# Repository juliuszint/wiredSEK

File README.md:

# A wired version of the Surface Ergonomic Keyboard from Microsoft.

## Disassembly
**Disclaimer**: These disassembly instructions can not be reversed and result in a broke keyboard. They are only provided as a documentation for other people to read, so that they dont have to brick their keyboard. So with that out of the way lets get started.

The keyboard is held together by an awful lot of glue and some screws. I do not own a heat gun and so i started with carefully using a screwdriver to remove the wrist rest. Even with a heat gun i doubt that it is impossible, to remove it without damaging some plastic. As can be seen in the following image, there is not only glue on the edges, but also in the center of the wrist rest.

The next step is to remove all 10 screws. 4 of them are small and 6 are rather large and threaded into the plastic. Then disconnect the power and paring button connector from the logic board. Next up is getting the screw driver back out and start to remove the keyboard panel from the case. It is held in place by a glue stripe all around the edges, some glue right in the center of the keyboard, and 9 glue spots as one can see in the following image.

4 more large screws hold the logic board cover in place. With them removed we can lift up the logic board and see the 34 pin Flexible Flat Cable (FFC) that connects the keyboard matrix with the logic board. 2 of those 34 lanes are not routed, so only 32 are actually connected.

I hoped that by fully disassembling the keyboard, I would be able to learn more about the keyboard matrix, but this did not turn out to be true. Anyway, after i removed every single plastic rivet and removed the remaining screws, this is how a fully disassembled surface ergonomic keyboard looks like:

Once the metal backplate is removed, the keys can just be popped out. They are still kept in place by small metal sheets and the wires connecting them. With the keyboard fully disassembled, we can now start to measure the keyboard matrix.

## Figuring out the keyboard matrix

With [@Geends](https://github.com/Geend/) logic analyzer and other hardware, we started by probing the logic level of every pin when no key is pressed. Next we toggled every LED (total of 4) one after another and observed the changes. Armed with that information we were able to make a educated guess of the keyboard matrix and with the 16 channel logic analyzer we were able to determine the full keyboard matrix.

Initial testing results:

| Pin Number (top left = 0)| Logic Level without Keypress |                            Function                           |
|:------------------------:|:----------------------------:| --------------------------------------------------------------|
| 0                        |3V                            | Keyboard Matrix: Row 0                                        |
| 1                        |3V                            | Keyboard Matrix: Row 1                                        |
| 2                        |3V                            | Keyboard Matrix: Row 2                                        |
| 3                        |3V                            | Keyboard Matrix: Row 3                                        |
| 4                        |3V                            | Keyboard Matrix: Row 4                                        |
| 5                        |3V                            | Keyboard Matrix: Row 5                                        |
| 6                        |3V                            | Keyboard Matrix: Row 6                                        |
| 7                        |3V                            | Keyboard Matrix: Row 7                                        |
| 8                        |3V                            | NumLink LED - with 3V the LED is off and on with 0.4V         |
| 9                        |3V                            | CapsLock LED - with 3V the LED is off and on with 0.4V        |
| 10                       |GND                           | Not connected                                                 |
| 11                       |1V                            | Pairing LED - White                                           |
| 12                       |1V                            | Pairing LED - Red                                             |
| 13                       |3V                            | LED Vcc                                                       |
| 14                       |0V                            | Keyboard Matrix: Column 0                                     |
| 15                       |0V                            | Keyboard Matrix: Column 1                                     |
| 16                       |0V                            | Keyboard Matrix: Column 2                                     |
| 17                       |0V                            | Keyboard Matrix: Column 3                                     |
| 18                       |0V                            | Keyboard Matrix: Column 4                                     |
| 19                       |0V                            | Keyboard Matrix: Column 5                                     |
| 20                       |0V                            | Keyboard Matrix: Column 6                                     |
| 21                       |0V                            | Keyboard Matrix: Column 7                                     |
| 22                       |0V                            | Keyboard Matrix: Column 8                                     |
| 23                       |0V                            | Keyboard Matrix: Column 9                                     |
| 24                       |0V                            | Keyboard Matrix: Column 10                                    |
| 25                       |0V                            | Keyboard Matrix: Column 11                                    |
| 26                       |0V                            | Keyboard Matrix: Column 12                                    |
| 27                       |0V                            | Keyboard Matrix: Column 13                                    |
| 28                       |0V                            | Keyboard Matrix: Column 14                                    |
| 29                       |0V                            | Keyboard Matrix: Column 15                                    |
| 30                       |0V                            | Keyboard Matrix: Column 16                                    |
| 31                       |3V                            | Fn LED - with 3V the LED is off and on with 0.4V              |
| 32                       |3V                            | Rollen - with 3V the LED is off and on with 0.4V              |
| 33                       |GND                           | Not connected                                                 |

The keyboard matrix from Surface Ergonomic Keyboard with german keys:

|           |    Row-0   |    Row-1   |    Row-2   |    Row-3   |    Row-4   |    Row-5   |    Row-6   |    Row-7   |
|:---------:|:----------:|:----------:|:----------:|:----------:|:----------:|:----------:|:----------:|:----------:|
| Column-0  |Num Entf    |Num 3       |Num 6       |Num 9       |Num \*      |6           |V           |L           |
| Column-1  |Num 0       |Num 2       |Num 5       |Num 8       |Num /       |5           |C           |K           |
| Column-2  |<           |Num 1       |Num 4       |Num 7       |Calc        |Num Enter   |X           |J           |
| Column-3  |Y           |T           |R           |E           |W           |Q           |Pfeil oben  |H           |
| Column-4  |-           |Bild Unten  |Bild Hoch   |Ende        |Num Lock    |Druck       |F12         |Leer        |
| Column-5  |.           |F4          |Entf        |Pos1        |Tab         |Einfg       |F11         |G           |
| Column-6  |,           |#           |0           |            |O           |Num +       |F10         |F           |
| Column-7  |M           |Ä           |9           |+           |i           |\`          |F9          |D           |
| Column-8  |N           |Num -       |8           |Ü           |U           |ß           |F8          |S           |
| Column-9  |Backspace   |Arrow right |7           |P           |Z           |^           |F7          |A           |
| Column-10 |Left Ctrl   |            |            |            |Right Ctrl  |            |            |            |
| Column-11 |            |Left Shift  |            |            |            |Right Shift |            |Fn          |
| Column-12 |            |            |Left ALT    |            |            |            |Alt Gr      |Context Menu|
| Column-13 |Pause       |Rollen      |Chat        |Left WIN    |Lock        |Rechteck    |            |Right WIN   |
| Column-14 |Num Clear   |4           |F1          |F5          |            |3           |Caps Lock   |Arrow Down  |
| Column-15 |            |F2          |F6          |Enter       |F3          |2           |            |Arrow Left  |
| Column-16 |Esc         |            |            |            |            |1           |B           |Ö           |

## Designing the PCB

The most difficult part was to find a MCU due to the chip shortage. From all the compatible controllers that are listed on QMKs website only the AT90USB646 was available. This turned out to be a perfect fit. It is a very simple MCU with enough GPIO pins, USB and a 64-TQFP package can be soldered by hand.

There is not much to say about the schematic itself because there is not a lot more on it then the MCU and a USB jack. There are a lot of testpoints, a power LED that can be disabled with a solder jumper, a status LED and a JTAG interface.

The complete board was designed with the open source software Kicad and tutorials from the Youtube channel Phil's Lab. This [[2]] three hour video is a great resource if someone wants to learn how to create a board from scratch and have it manufactured.

The outline and four holes (two placeholder and two for screws) are required for the circuit board to fit inside the keyboard. The position of the FFC/FPC connector is also fixed while the rest is up to us. 

The USB connector was the most difficult part to place. Because the keyboard is glued together and cannot be easily opened without damaging it, the plan is to make a small cutout where the PCB is located. So in a perfect world the connector would not need any more space than what is neccessary to switch the board. I managed this by using a right angle USB connector on the back of the PCB.

## PCB assembly

The USB connector, the FFC/FPC connector and the MCU had to be soldered by hand. Everything else was done by JLCPCB. These were the exact parts that i ordered. I included the USB cable not only because i like completeness, but also because not every cable will work. Between the USB connector and the PCB is only a limited amount of space for the plug.

* [FFC/FPC Connector](https://www.digikey.de/product-detail/de/F52R-1A7H1-11034/609-F52R-1A7H1-11034DKR-ND/11564783?itemSeq=366870776)
* [AT90USB646-AUR](https://www.digikey.de/product-detail/de/microchip-technology/AT90USB646-AUR/AT90USB646-AURCT-ND/3789393)
* [Micro USB Receptacle](https://www.digikey.de/product-detail/de/amphenol-icc-commercial-products/GMCB05801124EU/664-GMCB05801124EUTR-ND/13683048)
* [USB-Cabel](https://www.otto.de/p/primewire-premium-micro-usb-auf-usb-kabel-usb-a-stecker-auf-micro-b-stecker-600433312/#variationId=604008783)

## Keyboard (dis)assembly

Now we need a way to put our new PCB in. The `mask.odg` document contains a template that i used to mark the exact cutout. I printed it, glued it to cardboard and then used a box cutter to finish the stencil. To align it just use the side with the angled corners, put them into the battery compartment and then draw the inner lines. The rectangle at the top marks the position where the Flexible Flat Cable runs. In my first attempt this was not there and i bricked a keyboard :(. So to make sure this wont happen again, its important to first leave it there and after removing the rest, very carefully start to remove it by cutting only to a third of the depth and then break it.

The only thing left is to remove the PCB cover. There are 4 screws in total holding it in place. Two of which we can just open and then we have to just remove it by pulling up on the left side until the two arms on the right side break (does not take that much force).

## Firmware

Quantum Mechanical Keyboard (QMK) Firmware [[3]] is, as the name suggests, an open source firmware for keyboards. It powers the Moonlander and ErgoDoxEZ from ZSA and in general is super awesome and easy to customize. Even for completly custom keyboards like this one it is incredibly easy to get started.

The added code can be found in my  of the QMK repository on the wiredSEK branch. Basically the changes boil down to adding a new directory `keyboards/handwired/wiredSEK` and filling it with code that tells QMK what MCU it will be running on, which pins are connected to the keyboard matrix and what the keyboard layout should look like.

Everything that is left to do is to compile and flash the firmware with the follwing commands:
```
# compile
qmk compile -kb handwired/wiredsek -km default

# flash
sudo dfu-programmer at90usb646 erase --force
sudo dfu-programmer at90usb646 flash handwired_wiredsek_default.hex
sudo dfu-programmer at90usb646 launch
```

## The finished Keyboard

The only remaining question should be: **Why?** I would be lying if i told you that this project was not fun for me but this is not the only reason. As a programmer you type **a lot**. It therefore makes perfect sense to spend some time and optimize the device that you use to insert every single character.

I stopped counting the keyboards that i used. From a 10$ standard Logitech keyboard up to a Moonlander from ZSA i tried pretty much everything. The Surface Ergnomic Keyboard from Microsoft and the Moonlander from ZSA were the ones i liked the most, sadly for different reasons.

The Alcantara wrist rest, the keytravel, the switches and the ergonomic layout are the things that i enjoyed most while using the keyboard from Microsoft. Obviously the biggest downside for me was that it only connected via Bluetooth. It was laggy, could only be connected to a single computer and if you did not type for a few seconds, the keyboard went directly to sleep and it takes about a second for it to wake up while forgetting the key you pressed. Very annoying.

## Related Work
Chad Austin made a wired version of the Sculpt Ergonomic Keyboard [[1]].
 
[1]: https://chadaustin.me/2021/02/wired-sculpt/
[2]: https://www.youtube.com/watch?v=C7-8nUU6e3E
[3]: https://docs.qmk.fm/#/

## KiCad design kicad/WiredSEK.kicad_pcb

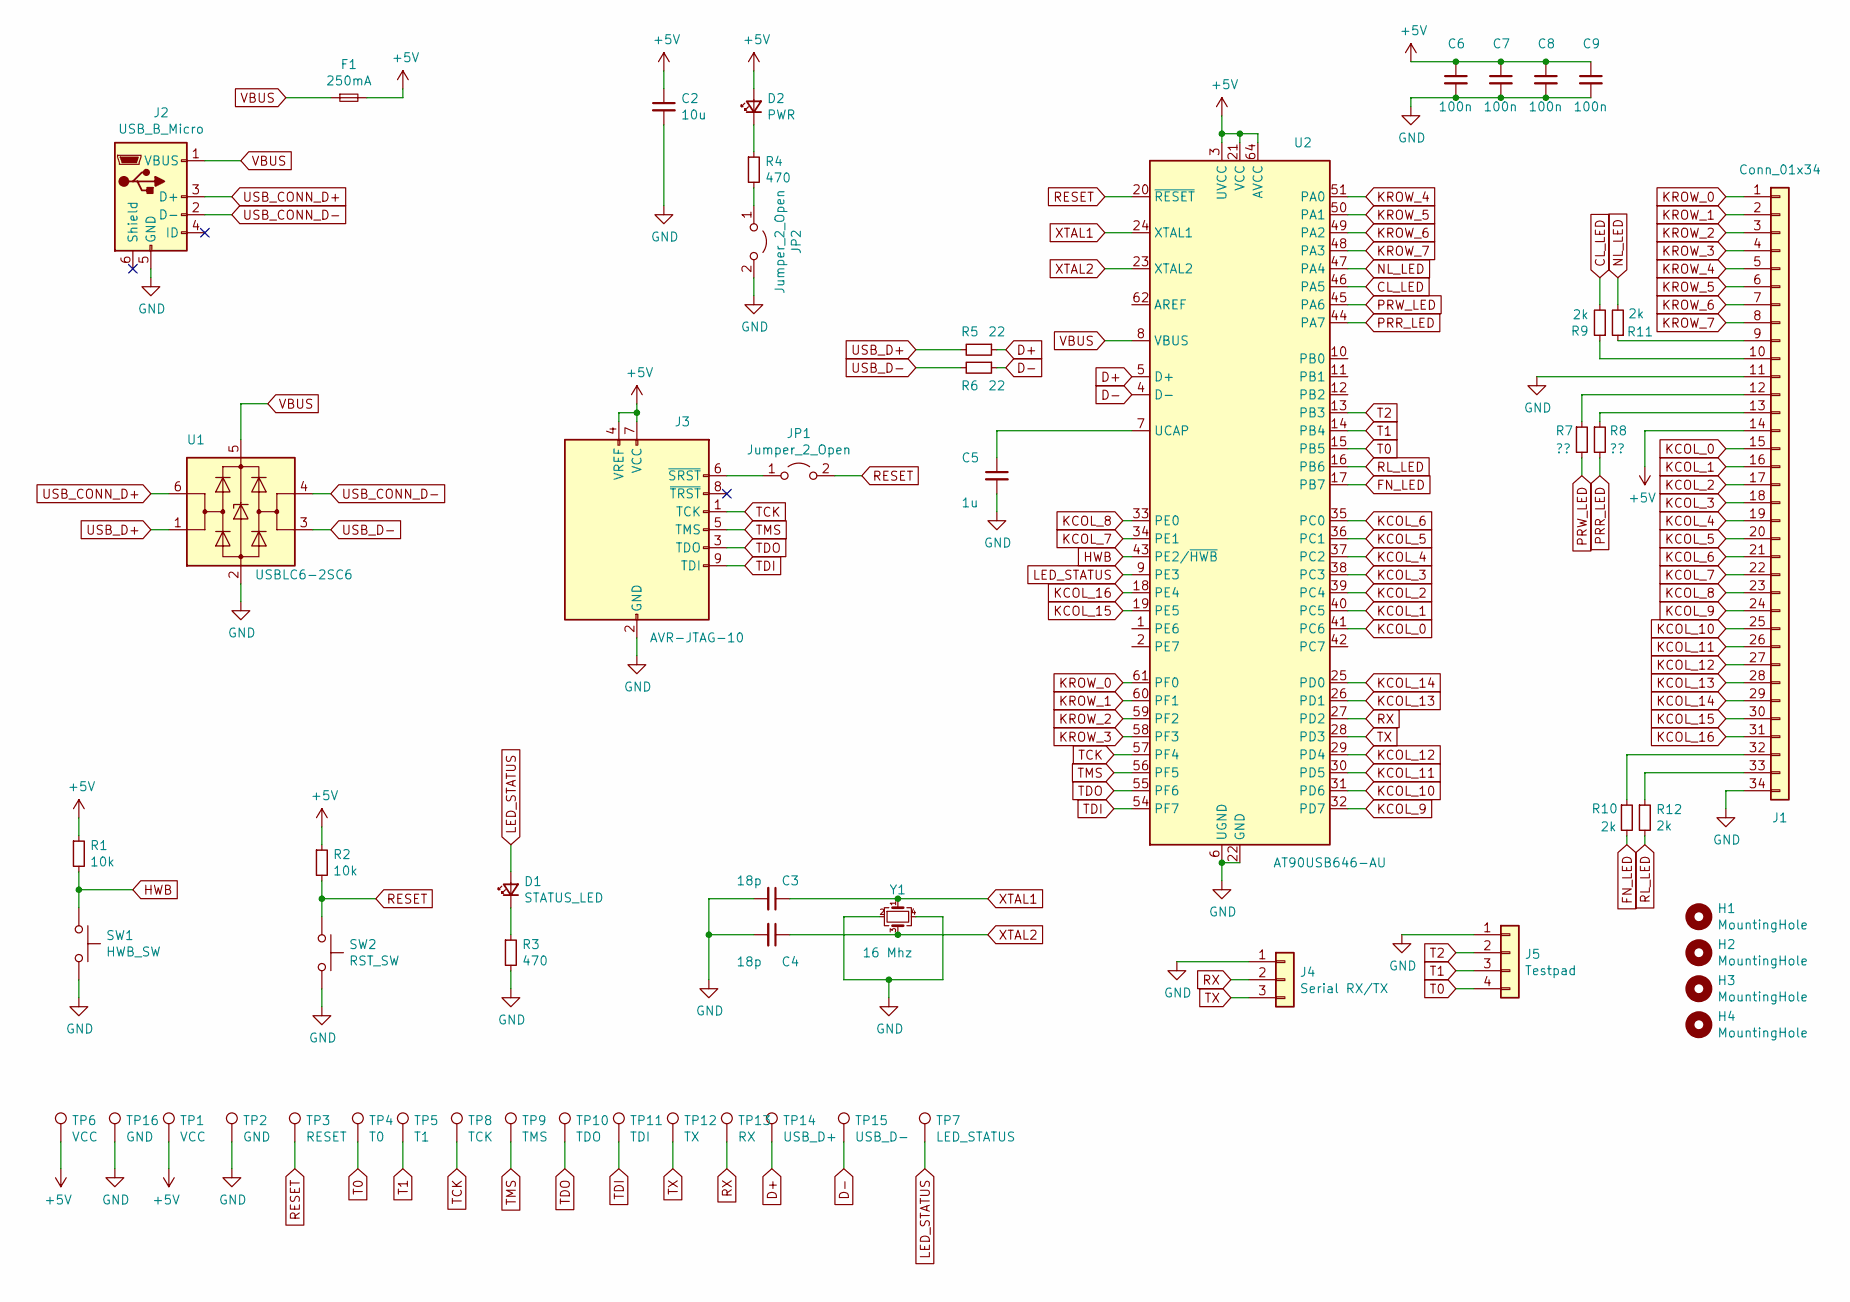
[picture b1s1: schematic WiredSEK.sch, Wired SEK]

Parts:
C2: 10u; C_0805_2012Metric_Pad1.18x1.45mm_HandSolder; LCSC Part # C15850
C3, C4: 18p; C_0603_1608Metric_Pad1.08x0.95mm_HandSolder; LCSC Part # C1647
C5: 1u; C_0603_1608Metric_Pad1.08x0.95mm_HandSolder; LCSC Part # C15849
C6, C7, C8, C9: 100n; C_0603_1608Metric_Pad1.08x0.95mm_HandSolder; LCSC Part # C57112
D1: STATUS_LED; LED_0603_1608Metric_Pad1.05x0.95mm_HandSolder; LCSC Part # C72041
D2: PWR; LED_0603_1608Metric_Pad1.05x0.95mm_HandSolder; LCSC Part # C72043
F1: 250mA; Fuse_1206_3216Metric_Pad1.42x1.75mm_HandSolder; LCSC Part # C369159
H1, H2: MountingHole; MountingHole_3mm
H3, H4: MountingHole; MountingHole_2.5mm
J1: Conn_01x34; F52R-1A7H1-11034
J2: USB_B_Micro; GMCB05801124EU
J3: AVR-JTAG-10; PinHeader_2x05_P2.54mm_Vertical
J4: Serial RX/TX; PinHeader_1x03_P2.54mm_Vertical
J5: Testpad; PinHeader_1x04_P2.54mm_Vertical
JP1, JP2: Jumper_2_Open; SolderJumper-2_P1.3mm_Open_RoundedPad1.0x1.5mm
R1, R2: 10k; R_0805_2012Metric_Pad1.20x1.40mm_HandSolder; LCSC Part # C17414
R3, R4: 470; R_0805_2012Metric_Pad1.20x1.40mm_HandSolder; LCSC Part # C17710
R5, R6: 22; R_0805_2012Metric_Pad1.20x1.40mm_HandSolder; LCSC Part # C25295
R7, R8: ??; R_0805_2012Metric_Pad1.20x1.40mm_HandSolder
R9, R10, R11, R12: 2k; R_0805_2012Metric_Pad1.20x1.40mm_HandSolder; LCSC Part # C17710
SW1: HWB_SW; SKRKAEE020; LCSC Part # C115357
SW2: RST_SW; SKRKAEE020; LCSC Part # C115357
TP1, TP6: VCC; TestPoint_Pad_D1.5mm
TP2, TP16: GND; TestPoint_Pad_D1.5mm
TP3: RESET; TestPoint_Pad_D1.5mm
TP4: T0; TestPoint_Pad_D1.5mm
TP5: T1; TestPoint_Pad_D1.5mm
TP7: LED_STATUS; TestPoint_Pad_D1.5mm
TP8: TCK; TestPoint_Pad_D1.5mm
TP9: TMS; TestPoint_Pad_D1.5mm
TP10: TDO; TestPoint_Pad_D1.5mm
TP11: TDI; TestPoint_Pad_D1.5mm
TP12: TX; TestPoint_Pad_D1.5mm
TP13: RX; TestPoint_Pad_D1.5mm
TP14: USB_D+; TestPoint_Pad_D1.5mm
TP15: USB_D-; TestPoint_Pad_D1.5mm
U1: USBLC6-2SC6; SOT-23-6; LCSC Part # C558442
U2: AT90USB646-AU; TQFP-64_14x14mm_P0.8mm
Y1: 16 Mhz; Crystal_SMD_3225-4Pin_3.2x2.5mm_HandSoldering; LCSC Part # X1E000021011900

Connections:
+5V: C2.1, C6.1, C7.1, C8.1, C9.1, D2.2 (A), F1.2, J1.14, J3.4 (VREF), J3.7 (VCC), R1.1, R2.1, TP1.1, TP6.1, U2.3 (UVCC), U2.21 (VCC), U2.52 (VCC), U2.64 (AVCC)
CL_LED: R9.2, U2.46 (PA5)
D+: R5.1, TP14.1, U2.5 (D+)
D-: R6.1, TP15.1, U2.4 (D-)
FN_LED: R10.2, U2.17 (PB7)
GND: C2.2, C3.2, C4.2, C5.2, C6.2, C7.2, C8.2, C9.2, J1.11, J1.34, J2.5 (GND), J3.2 (GND), J3.10 (GND), J4.1, J5.1, JP2.2 (B), R3.2, SW1.2, SW2.2, TP2.1, TP16.1, U1.2 (GND), U2.6 (UGND), U2.22 (GND), U2.53 (GND), U2.63 (GND), Y1.2, Y1.4
HWB: R1.2, SW1.1, U2.43 (PE2/~HWB)
KCOL_0: J1.15, U2.41 (PC6)
KCOL_1: J1.16, U2.40 (PC5)
KCOL_2: J1.17, U2.39 (PC4)
KCOL_3: J1.18, U2.38 (PC3)
KCOL_4: J1.19, U2.37 (PC2)
KCOL_5: J1.20, U2.36 (PC1)
KCOL_6: J1.21, U2.35 (PC0)
KCOL_7: J1.22, U2.34 (PE1)
KCOL_8: J1.23, U2.33 (PE0)
KCOL_9: J1.24, U2.32 (PD7)
KCOL_10: J1.25, U2.31 (PD6)
KCOL_11: J1.26, U2.30 (PD5)
KCOL_12: J1.27, U2.29 (PD4)
KCOL_13: J1.28, U2.26 (PD1)
KCOL_14: J1.29, U2.25 (PD0)
KCOL_15: J1.30, U2.19 (PE5)
KCOL_16: J1.31, U2.18 (PE4)
KROW_0: J1.1, U2.61 (PF0)
KROW_1: J1.2, U2.60 (PF1)
KROW_2: J1.3, U2.59 (PF2)
KROW_3: J1.4, U2.58 (PF3)
KROW_4: J1.5, U2.51 (PA0)
KROW_5: J1.6, U2.50 (PA1)
KROW_6: J1.7, U2.49 (PA2)
KROW_7: J1.8, U2.48 (PA3)
LED_STATUS: D1.2 (A), TP7.1, U2.9 (PE3)
NL_LED: R11.2, U2.47 (PA4)
unnamed: C5.1, U2.7 (UCAP)
unnamed: D1.1 (K), R3.1
unnamed: D2.1 (K), R4.1
unnamed: J1.9, R11.1
unnamed: J1.10, R9.1
unnamed: J1.12, R7.1
unnamed: J1.13, R8.1
unnamed: J1.32, R10.1
unnamed: J1.33, R12.1
unnamed: J3.6 (~SRST), JP1.1 (A)
unnamed: JP2.1 (A), R4.2
PRR_LED: R8.2, U2.44 (PA7)
PRW_LED: R7.2, U2.45 (PA6)
RESET: JP1.2 (B), R2.2, SW2.1, TP3.1, U2.20 (~RESET)
RL_LED: R12.2, U2.16 (PB6)
RX: J4.2, TP13.1, U2.27 (PD2)
T0: J5.4, TP4.1, U2.15 (PB5)
T1: J5.3, TP5.1, U2.14 (PB4)
T2: J5.2, U2.13 (PB3)
TCK: J3.1 (TCK), TP8.1, U2.57 (PF4)
TDI: J3.9 (TDI), TP11.1, U2.54 (PF7)
TDO: J3.3 (TDO), TP10.1, U2.55 (PF6)
TMS: J3.5 (TMS), TP9.1, U2.56 (PF5)
TX: J4.3, TP12.1, U2.28 (PD3)
USB_CONN_D+: J2.3 (D+), U1.6 (I/O1)
USB_CONN_D-: J2.2 (D-), U1.4 (I/O2)
USB_D+: R5.2, U1.1 (I/O1)
USB_D-: R6.2, U1.3 (I/O2)
VBUS: F1.1, J2.1 (VBUS), U1.5 (VBUS), U2.8 (VBUS)
XTAL1: C3.1, U2.24 (XTAL1), Y1.1
XTAL2: C4.1, U2.23 (XTAL2), Y1.3

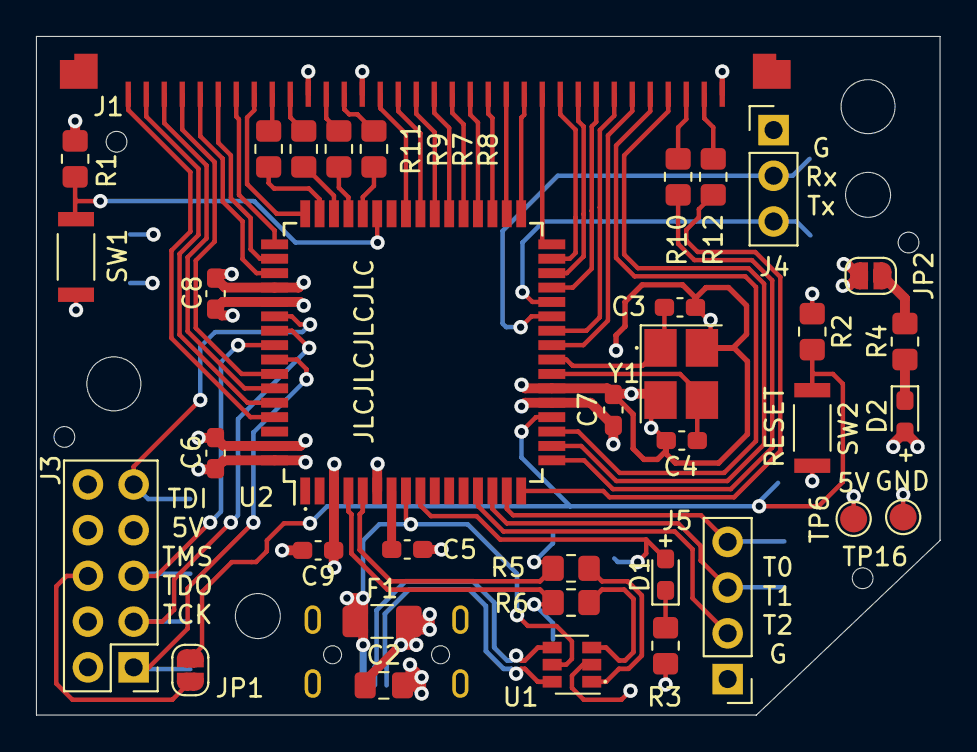
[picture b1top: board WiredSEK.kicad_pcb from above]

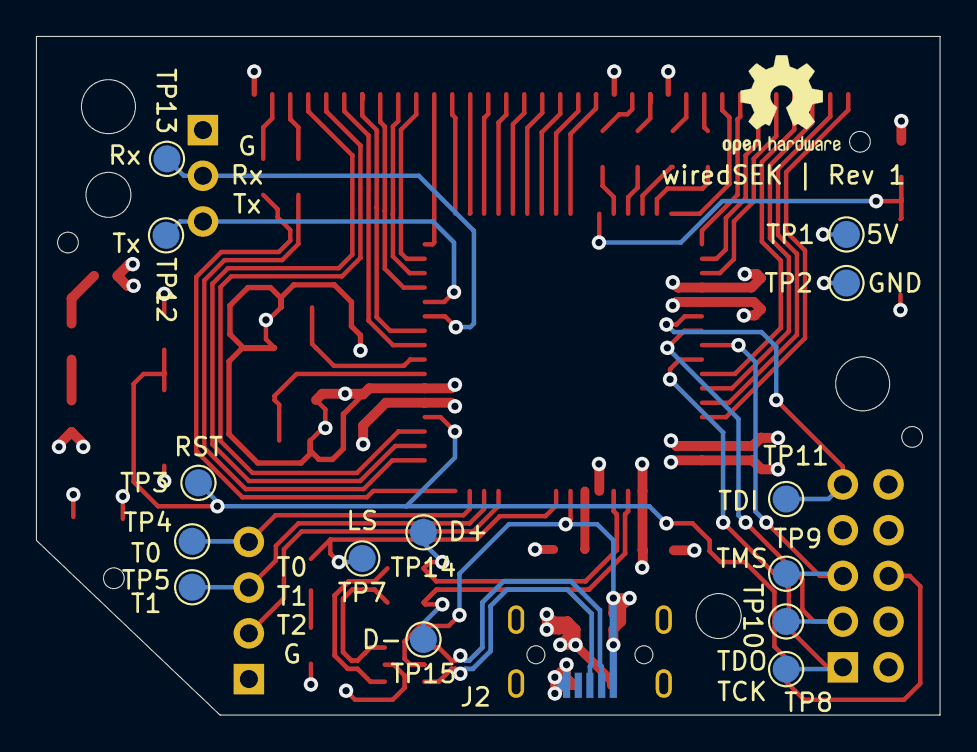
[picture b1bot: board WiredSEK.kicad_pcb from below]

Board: 4 copper layers, 50.2 x 37.7 mm, 55 parts (15 on the bottom side), 65 nets.

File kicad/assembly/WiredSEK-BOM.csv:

Comment,Designator,Footprint,LCSC
"10u","C2","Capacitor_SMD:C_0805_2012Metric_Pad1.18x1.45mm_HandSolder","C15850"
"18p","C3,C4","Capacitor_SMD:C_0603_1608Metric_Pad1.08x0.95mm_HandSolder","C1647"
"1u","C5","Capacitor_SMD:C_0603_1608Metric_Pad1.08x0.95mm_HandSolder","C15849"
"100n","C6,C7,C8,C9","Capacitor_SMD:C_0603_1608Metric_Pad1.08x0.95mm_HandSolder","C57112"
"STATUS_LED","D1","LED_SMD:LED_0603_1608Metric_Pad1.05x0.95mm_HandSolder","C72041"
"PWR","D2","LED_SMD:LED_0603_1608Metric_Pad1.05x0.95mm_HandSolder","C72043"
"250mA","F1","Fuse:Fuse_1206_3216Metric_Pad1.42x1.75mm_HandSolder","C369159"
"MountingHole","H1,H2","MountingHole:MountingHole_3mm",""
"MountingHole","H3,H4","MountingHole:MountingHole_2.5mm",""
"Conn_01x34","J1","WiredSEK:F52R-1A7H1-11034",""
"USB_B_Micro","J2","WiredSEK:GMCB05801124EU",""
"AVR-JTAG-10","J3","Connector_PinHeader_2.54mm:PinHeader_2x05_P2.54mm_Vertical",""
"Serial RX/TX","J4","Connector_PinHeader_2.54mm:PinHeader_1x03_P2.54mm_Vertical",""
"Testpad","J5","Connector_PinHeader_2.54mm:PinHeader_1x04_P2.54mm_Vertical",""
"Jumper_2_Open","JP1,JP2","Jumper:SolderJumper-2_P1.3mm_Open_RoundedPad1.0x1.5mm",""
"2k","R8,R9,R10,R11,R12","Resistor_SMD:R_0805_2012Metric_Pad1.20x1.40mm_HandSolder","C17710"
"10k","R1,R2,R7","Resistor_SMD:R_0805_2012Metric_Pad1.20x1.40mm_HandSolder","C17414"
"470","R3,R4","Resistor_SMD:R_0805_2012Metric_Pad1.20x1.40mm_HandSolder","C17710"
"22","R5,R6","Resistor_SMD:R_0805_2012Metric_Pad1.20x1.40mm_HandSolder","C25295"
"HWB_SW","SW1","WiredSEK:SKRKAEE020","C115357"
"RST_SW","SW2","WiredSEK:SKRKAEE020","C115357"
"VCC","TP1,TP6","TestPoint:TestPoint_Pad_D1.5mm",""
"TDO","TP10","TestPoint:TestPoint_Pad_D1.5mm",""
"TDI","TP11","TestPoint:TestPoint_Pad_D1.5mm",""
"TX","TP12","TestPoint:TestPoint_Pad_D1.5mm",""
"RX","TP13","TestPoint:TestPoint_Pad_D1.5mm",""
"USB_D+","TP14","TestPoint:TestPoint_Pad_D1.5mm",""
"USB_D-","TP15","TestPoint:TestPoint_Pad_D1.5mm",""
"GND","TP2,TP16","TestPoint:TestPoint_Pad_D1.5mm",""
"RESET","TP3","TestPoint:TestPoint_Pad_D1.5mm",""
"T0","TP4","TestPoint:TestPoint_Pad_D1.5mm",""
"T1","TP5","TestPoint:TestPoint_Pad_D1.5mm",""
"LED_STATUS","TP7","TestPoint:TestPoint_Pad_D1.5mm",""
"TCK","TP8","TestPoint:TestPoint_Pad_D1.5mm",""
"TMS","TP9","TestPoint:TestPoint_Pad_D1.5mm",""
"USBLC6-2SC6","U1","Package_TO_SOT_SMD:SOT-23-6","C558442"
"AT90USB646-AU","U2","Package_QFP:TQFP-64_14x14mm_P0.8mm",""
"16 Mhz","Y1","Crystal:Crystal_SMD_3225-4Pin_3.2x2.5mm_HandSoldering","C13738"

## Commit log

2021-06-18 added a license
2021-06-18 moved kicad files out of subfolder
2021-06-18 added disassembly process in readme
2021-06-18 added smaller preview images
2021-06-19 added keyboard matrix measurement results
2021-07-17 fixed typo, switched row and column, and added more information after new reverse engineering session
2021-07-18 done with pcb routing
2021-07-21 Fixed SW1 and SW2 footprints and cleaned silk layers
2021-07-23 preparing for jlcpcb order
2021-07-23 added pin 1 and polarity markers
2021-07-23 switched row and column in secondary table
2021-08-02 JLCPCB Order REV 1
2021-09-09 switched column 2 and 3 after testing
2021-09-09 added right shift location in matrix
2021-09-14 added small sample c program for testing the board
2021-09-15 added the pcb section
2021-09-16 project documentation
2021-09-21 added mask template
2021-09-22 keyboard (dis)assembly
2021-09-24 firmware section
